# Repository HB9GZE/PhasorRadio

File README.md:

# PhasorRadio
Phasor-Radio for 20m/40m and 80m with 5 Watt ERP Amp

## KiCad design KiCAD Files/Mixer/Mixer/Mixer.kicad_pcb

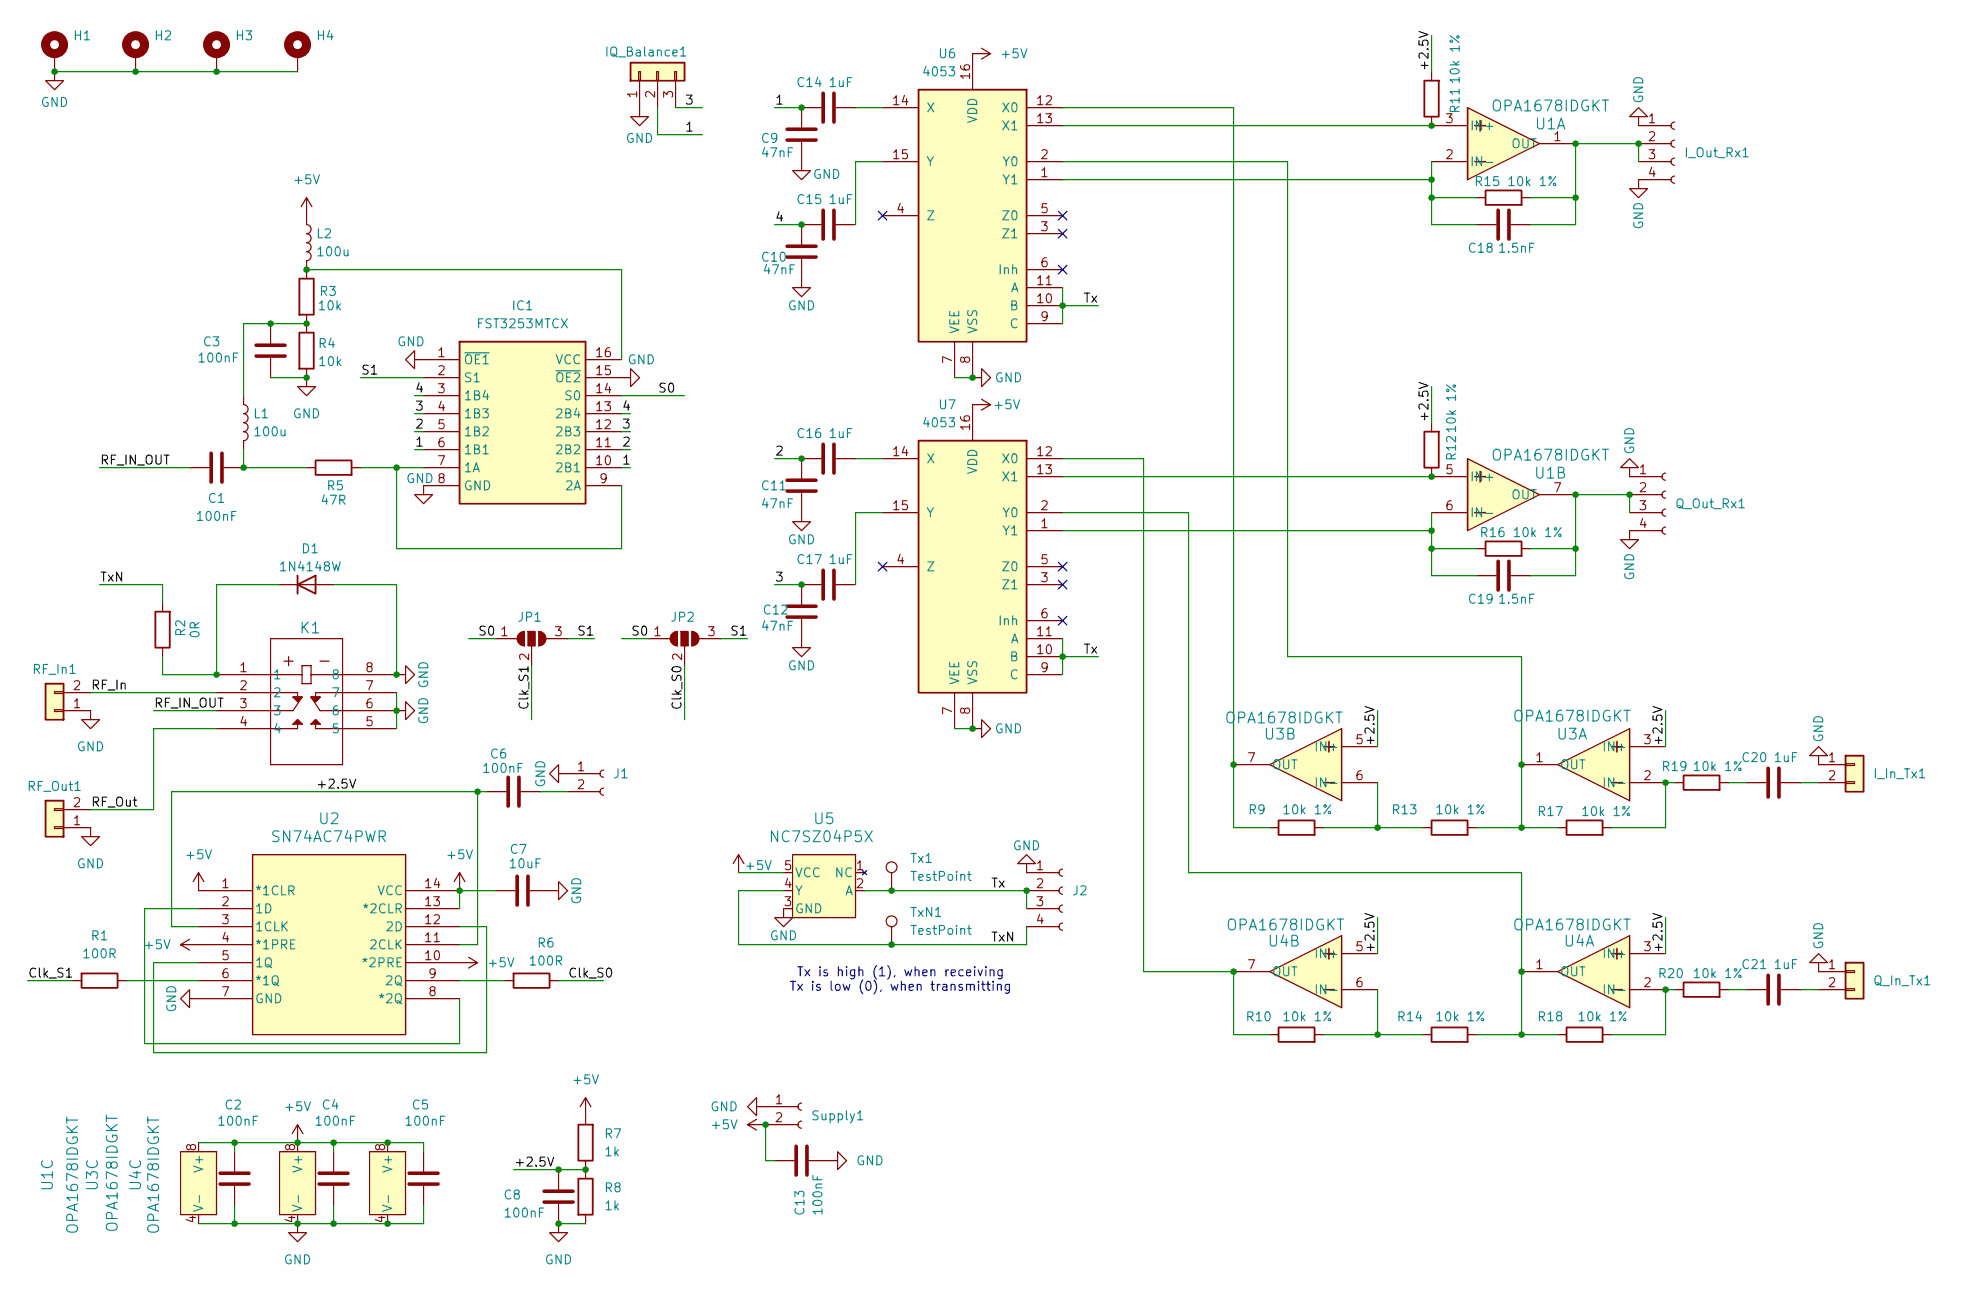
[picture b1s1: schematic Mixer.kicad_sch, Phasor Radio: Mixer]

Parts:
C1, C2, C3, C4, C5, C8, C13: 100nF; C_0805_2012Metric_Pad1.18x1.45mm_HandSolder
C6: 100nF; C_0603_1608Metric_Pad1.08x0.95mm_HandSolder
C7: 10uF; C_0805_2012Metric_Pad1.18x1.45mm_HandSolder
C9, C10, C11, C12: 47nF; C_0805_2012Metric_Pad1.18x1.45mm_HandSolder
C14, C15, C16, C17, C20, C21: 1uF; C_0805_2012Metric_Pad1.18x1.45mm_HandSolder
C18, C19: 1.5nF; C_0805_2012Metric_Pad1.18x1.45mm_HandSolder
D1: 1N4148W; D_SOD-123
H1, H2, H3, H4: MountingHole_Pad; MountingHole_2.7mm_M2.5_DIN965_Pad_TopBottom
IC1: FST3253MTCX; SOP65P640X110-16N; Manufacturer_Part_Number FST3253MTCX; Mouser Part Number 512-FST3253MTCX
IQ_Balance1: Conn_01x03; PinHeader_1x03_P1.00mm_Vertical
I_In_Tx1: Conn_01x02; JST_EH_B2B-EH-A_1x02_P2.50mm_Vertical
I_Out_Rx1: Conn_01x04_Socket; JST_EH_B4B-EH-A_1x04_P2.50mm_Vertical
J1: Conn_01x02_Socket; JST_EH_B2B-EH-A_1x02_P2.50mm_Vertical
J2: Conn_01x04_Socket; JST_EH_B4B-EH-A_1x04_P2.50mm_Vertical
JP1, JP2: SolderJumper_3_Open; SolderJumper-3_P1.3mm_Open_Pad1.0x1.5mm_NumberLabels
K1: G6K-2F-Y DC3; G6K-2F-Y DC3_OMR
L1, L2: 100u; L_0805_2012Metric_Pad1.15x1.40mm_HandSolder
Q_In_Tx1: Conn_01x02; JST_EH_B2B-EH-A_1x02_P2.50mm_Vertical
Q_Out_Rx1: Conn_01x04_Socket; JST_EH_B4B-EH-A_1x04_P2.50mm_Vertical
R1, R6: 100R; R_0603_1608Metric_Pad0.98x0.95mm_HandSolder
R2: 0R; R_0805_2012Metric_Pad1.20x1.40mm_HandSolder
R3, R4: 10k; R_0805_2012Metric_Pad1.20x1.40mm_HandSolder
R5: 47R; R_0805_2012Metric_Pad1.20x1.40mm_HandSolder
R7, R8: 1k; R_0805_2012Metric_Pad1.20x1.40mm_HandSolder
R9, R10, R11, R12, R13, R14, R15, R16, R17, R18, R19, R20: 10k 1%; R_0805_2012Metric_Pad1.20x1.40mm_HandSolder
RF_In1: Conn_01x02; PinHeader_1x02_P2.54mm_Vertical
RF_Out1: Conn_01x02; PinHeader_1x02_P2.54mm_Vertical
Supply1: Conn_01x02_Socket; JST_EH_B2B-EH-A_1x02_P2.50mm_Vertical
Tx1: TestPoint; Pin_D0.7mm_L6.5mm_W1.8mm_FlatFork
TxN1: TestPoint; Pin_D0.7mm_L6.5mm_W1.8mm_FlatFork
U1, U3, U4: OPA1678IDGKT; OPA1678_L
U2: SN74AC74PWR; 74AC74-L
U5: NC7SZ04P5X; SC-88A-5_1P35X2P2_ONS
U6, U7: 4053; TSSOP16_5P1X4P5_NEX

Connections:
+5V: C2.2, C4.2, C5.2, C7.2, C13.2, L2.1, R7.2, Supply1.2, U1.8 (V+), U2.1 (*1CLR), U2.4 (*1PRE), U2.10 (*2PRE), U2.13 (*2CLR), U2.14 (VCC), U3.8 (V+), U4.8 (V+), U5.5 (VCC), U6.16 (VDD), U7.16 (VDD)
/1: C9.2, C14.2, IC1.6 (1B1), IC1.10 (2B1), IQ_Balance1.2
/2: C11.2, C16.2, IC1.5 (1B2), IC1.11 (2B2)
/3: C12.2, C17.2, IC1.4 (1B3), IC1.12 (2B3), IQ_Balance1.3
/4: C10.2, C15.2, IC1.3 (1B4), IC1.13 (2B4)
/+2.5V: C6.2, C8.2, R7.1, R8.1, R11.2, R12.2, U2.3 (1CLK), U2.11 (2CLK), U3.3 (IN+), U3.5 (IN+), U4.3 (IN+), U4.5 (IN+)
/Clk_S1: JP1.2 (C), R1.2
/RF_IN_OUT: C1.1, K1.3
/RF_In: K1.2, RF_In1.2
/RF_Out: K1.4, RF_Out1.2
/S1: IC1.2 (S1), JP1.3 (B), JP2.3 (B)
/Tx: J2.2, J2.3, Tx1.1, U5.2 (A), U6.9 (C), U6.10 (B), U6.11 (A), U7.9 (C), U7.10 (B), U7.11 (A)
/TxN: J2.4, R2.2, TxN1.1, U5.4 (Y)
GND: C2.1, C3.1, C4.1, C5.1, C7.1, C8.1, C9.1, C10.1, C11.1, C12.1, C13.1, D1.2 (A), H1.1, H2.1, H3.1, H4.1, IC1.1 (~OE1), IC1.8 (GND), IC1.15 (~OE2), IQ_Balance1.1, I_In_Tx1.1, I_Out_Rx1.1, I_Out_Rx1.4, J1.1, J2.1, K1.5, K1.6, K1.7, K1.8, Q_In_Tx1.1, Q_Out_Rx1.1, Q_Out_Rx1.4, R4.2, R8.2, RF_In1.1, RF_Out1.1, Supply1.1, U1.4 (V-), U2.7 (GND), U3.4 (V-), U4.4 (V-), U5.3 (GND), U6.7 (VEE), U6.8 (VSS), U7.7 (VEE), U7.8 (VSS)
unnamed: C1.2, L1.2, R5.1
unnamed: C3.2, L1.1, R3.2, R4.1
unnamed: C20.2, R19.2
unnamed: C21.2, R20.2
unnamed: D1.1 (K), K1.1, R2.1
unnamed: IC1.7 (1A), IC1.9 (2A), R5.2
unnamed: IC1.16 (VCC), L2.2, R3.1
unnamed: C20.1, I_In_Tx1.2
unnamed: C18.1, I_Out_Rx1.2, I_Out_Rx1.3, R15.2, U1.1 (OUT)
unnamed: C6.1, J1.2
unnamed: C21.1, Q_In_Tx1.2
unnamed: C19.1, Q_Out_Rx1.2, Q_Out_Rx1.3, R16.2, U1.7 (OUT)
unnamed: R11.1, U1.3 (IN+), U6.13 (X1)
unnamed: C18.2, R15.1, U1.2 (IN-), U6.1 (Y1)
unnamed: R12.1, U1.5 (IN+), U7.13 (X1)
unnamed: C19.2, R16.1, U1.6 (IN-), U7.1 (Y1)
unnamed: U2.5 (1Q), U2.12 (2D)
unnamed: R6.2, U2.9 (2Q)
unnamed: R1.1, U2.6 (*1Q)
unnamed: U2.2 (1D), U2.8 (*2Q)
unnamed: R17.2, R19.1, U3.2 (IN-)
unnamed: R13.2, R17.1, U3.1 (OUT), U6.2 (Y0)
unnamed: R9.2, R13.1, U3.6 (IN-)
unnamed: R9.1, U3.7 (OUT), U6.12 (X0)
unnamed: R18.2, R20.1, U4.2 (IN-)
unnamed: R14.2, R18.1, U4.1 (OUT), U7.2 (Y0)
unnamed: R10.2, R14.1, U4.6 (IN-)
unnamed: R10.1, U4.7 (OUT), U7.12 (X0)
unnamed: C14.1, U6.14 (X)
unnamed: C15.1, U6.15 (Y)
unnamed: C16.1, U7.14 (X)
unnamed: C17.1, U7.15 (Y)

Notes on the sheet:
Tx is high (1), when receiving Tx is low (0), when transmitting

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
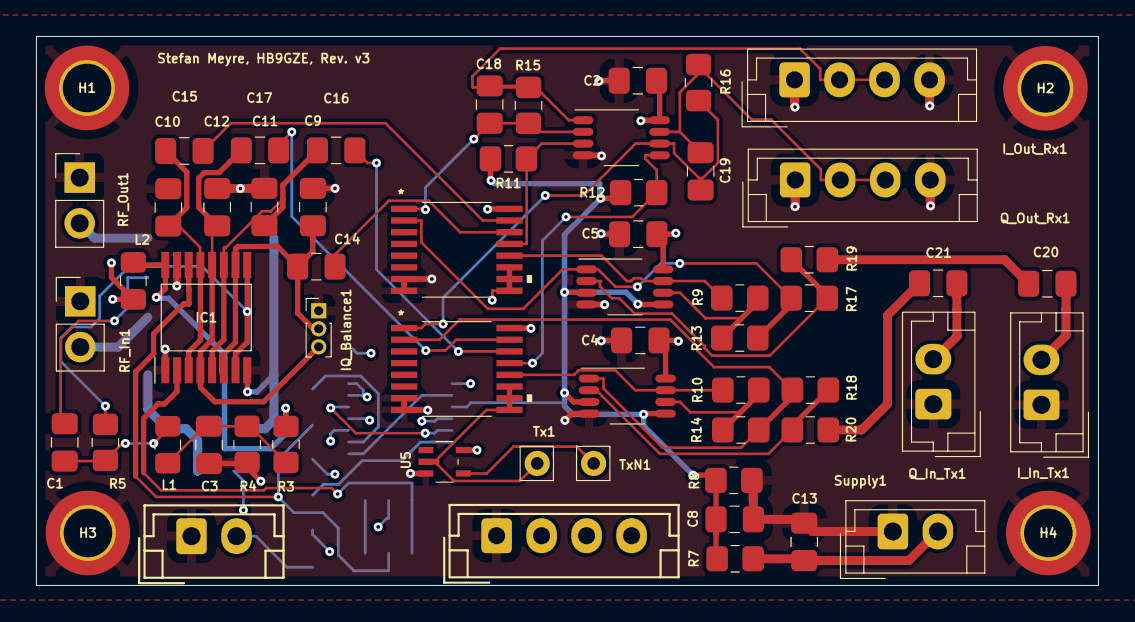
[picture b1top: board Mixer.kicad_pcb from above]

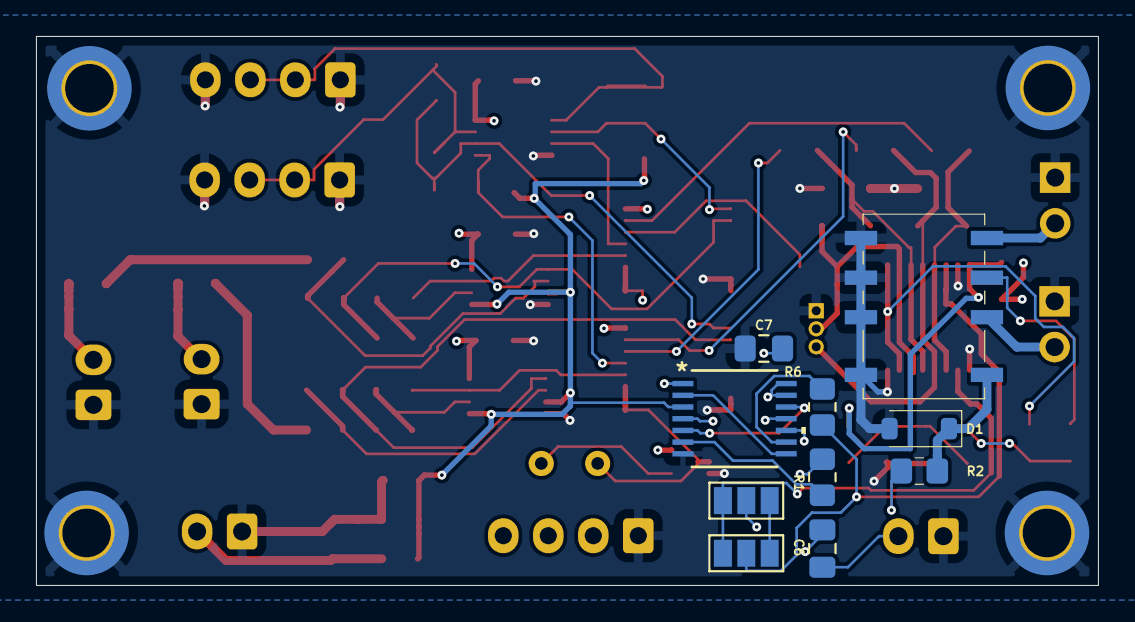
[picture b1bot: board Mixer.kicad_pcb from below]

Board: 4 copper layers, 59.0 x 30.5 mm, 71 parts (10 on the bottom side), 48 nets.

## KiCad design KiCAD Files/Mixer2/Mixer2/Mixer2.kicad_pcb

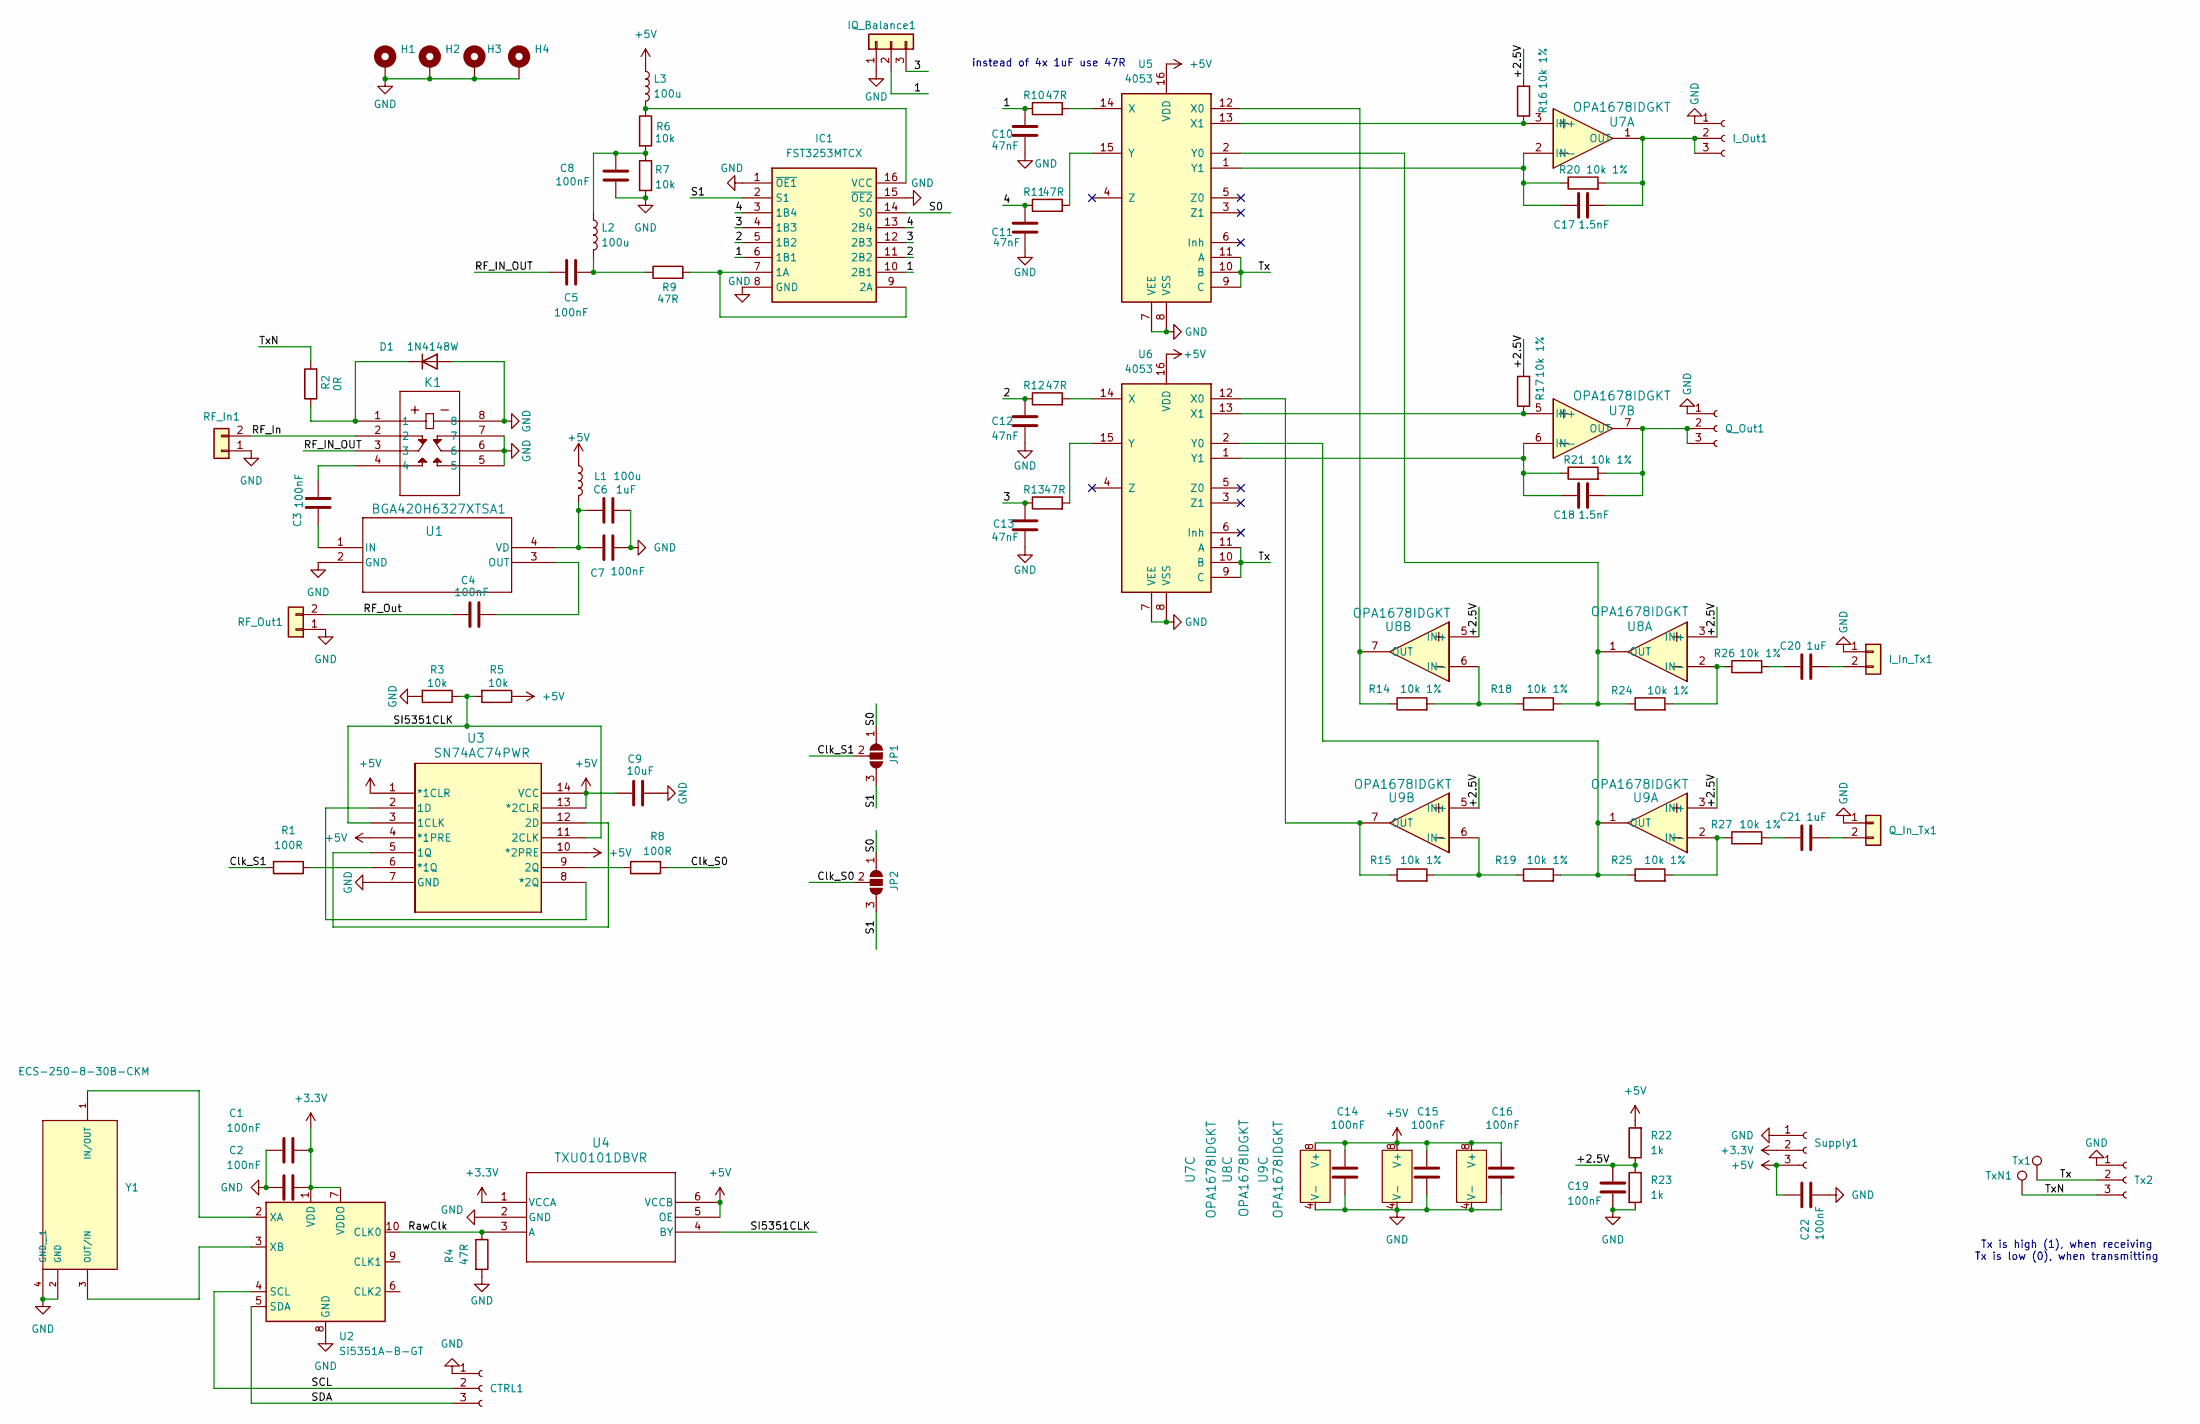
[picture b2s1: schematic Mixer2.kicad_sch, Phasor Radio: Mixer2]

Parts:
C1, C2, C3, C4, C5, C7, C8, C14, C15, C16, C19, C22: 100nF; C_0603_1608Metric_Pad1.08x0.95mm_HandSolder
C6, C20, C21: 1uF; C_0603_1608Metric_Pad1.08x0.95mm_HandSolder
C9: 10uF; C_0603_1608Metric_Pad1.08x0.95mm_HandSolder
C10, C11, C12, C13: 47nF; C_0603_1608Metric_Pad1.08x0.95mm_HandSolder
C17, C18: 1.5nF; C_0603_1608Metric_Pad1.08x0.95mm_HandSolder
CTRL1: Conn_01x03_Socket; JST_EH_B3B-EH-A_1x03_P2.50mm_Vertical
D1: 1N4148W; D_SOD-123
H1, H2, H3, H4: MountingHole_Pad; MountingHole_2.7mm_M2.5_DIN965_Pad_TopBottom
IC1: FST3253MTCX; SOP65P640X110-16N; Manufacturer_Part_Number FST3253MTCX; Mouser Part Number 512-FST3253MTCX
IQ_Balance1: Conn_01x03; PinHeader_1x03_P1.00mm_Vertical
I_In_Tx1: Conn_01x02; JST_EH_B2B-EH-A_1x02_P2.50mm_Vertical
I_Out1: I_Out; JST_EH_B3B-EH-A_1x03_P2.50mm_Vertical
JP1, JP2: SolderJumper_3_Open; SolderJumper-3_P1.3mm_Open_Pad1.0x1.5mm_NumberLabels
K1: G6K-2F-Y DC3; G6K-2F-Y DC3_OMR
L1, L2, L3: 100u; L_0805_2012Metric_Pad1.15x1.40mm_HandSolder
Q_In_Tx1: Conn_01x02; JST_EH_B2B-EH-A_1x02_P2.50mm_Vertical
Q_Out1: Q_Out; JST_EH_B3B-EH-A_1x03_P2.50mm_Vertical
R1, R8: 100R; R_0603_1608Metric_Pad0.98x0.95mm_HandSolder
R2: 0R; R_0603_1608Metric_Pad0.98x0.95mm_HandSolder
R3, R5, R6, R7: 10k; R_0603_1608Metric_Pad0.98x0.95mm_HandSolder
R4, R9, R10, R11, R12, R13: 47R; R_0603_1608Metric_Pad0.98x0.95mm_HandSolder
R14, R15, R16, R17, R18, R19, R20, R21, R24, R25, R26, R27: 10k 1%; R_0603_1608Metric_Pad0.98x0.95mm_HandSolder
R22, R23: 1k; R_0603_1608Metric_Pad0.98x0.95mm_HandSolder
RF_In1: Conn_01x02; PinHeader_1x02_P2.54mm_Vertical
RF_Out1: Conn_01x02; PinHeader_1x02_P2.54mm_Vertical
Supply1: Supply; JST_EH_B3B-EH-A_1x03_P2.50mm_Vertical
Tx1: TestPoint; Pin_D0.7mm_L6.5mm_W1.8mm_FlatFork
Tx2: Q_Out; JST_EH_B3B-EH-A_1x03_P2.50mm_Vertical
TxN1: TestPoint; Pin_D0.7mm_L6.5mm_W1.8mm_FlatFork
U1: BGA420H6327XTSA1; PG-SOT343-4-1_INF
U2: Si5351A-B-GT; MSOP-10_3x3mm_P0.5mm
U3: SN74AC74PWR; 74AC74-L
U4: TXU0101DBVR; SOT-23-6-DBV_TEX
U5, U6: 4053; TSSOP16_5P1X4P5_NEX
U7, U8, U9: OPA1678IDGKT; OPA1678_L
Y1: ECS-250-8-30B-CKM; XTAL_ECS-250-8-30B-CKM

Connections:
+3.3V: C1.2, C2.2, Supply1.2, U2.1 (VDD), U2.7 (VDDO), U4.1 (VCCA)
+5V: C9.2, C14.2, C15.2, C16.2, C22.2, L1.1, L3.1, R5.1, R22.2, Supply1.3, U3.1 (*1CLR), U3.4 (*1PRE), U3.10 (*2PRE), U3.13 (*2CLR), U3.14 (VCC), U4.5 (OE), U4.6 (VCCB), U5.16 (VDD), U6.16 (VDD), U7.8 (V+), U8.8 (V+), U9.8 (V+)
/1: C10.2, IC1.6 (1B1), IC1.10 (2B1), IQ_Balance1.2, R10.1
/2: C12.2, IC1.5 (1B2), IC1.11 (2B2), R12.1
/3: C13.2, IC1.4 (1B3), IC1.12 (2B3), IQ_Balance1.3, R13.1
/4: C11.2, IC1.3 (1B4), IC1.13 (2B4), R11.1
/+2.5V: C19.2, R16.2, R17.2, R22.1, R23.1, U8.3 (IN+), U8.5 (IN+), U9.3 (IN+), U9.5 (IN+)
/Clk_S0: JP2.2 (C), R8.1
/Clk_S1: JP1.2 (C), R1.2
/RF_IN_OUT: C5.1, K1.3
/RF_In: K1.2, RF_In1.2
/RF_Out: C4.2, RF_Out1.2
/RawClk: R4.1, U2.10 (CLK0), U4.3 (A)
/S0: IC1.14 (S0), JP1.1 (A), JP2.1 (A)
/S1: IC1.2 (S1), JP1.3 (B), JP2.3 (B)
/SCL: CTRL1.2, U2.4 (SCL)
/SDA: CTRL1.3, U2.5 (SDA)
/SI5351CLK: R3.1, R5.2, U3.3 (1CLK), U3.11 (2CLK), U4.4 (BY)
/Tx: Tx1.1, Tx2.2, U5.9 (C), U5.10 (B), U5.11 (A), U6.9 (C), U6.10 (B), U6.11 (A)
/TxN: R2.2, Tx2.3, TxN1.1
GND: C1.1, C2.1, C6.1, C7.1, C8.1, C9.1, C10.1, C11.1, C12.1, C13.1, C14.1, C15.1, C16.1, C19.1, C22.1, CTRL1.1, D1.2 (A), H1.1, H2.1, H3.1, H4.1, IC1.1 (~OE1), IC1.8 (GND), IC1.15 (~OE2), IQ_Balance1.1, I_In_Tx1.1, I_Out1.1, K1.5, K1.6, K1.7, K1.8, Q_In_Tx1.1, Q_Out1.1, R3.2, R4.2, R7.2, R23.2, RF_In1.1, RF_Out1.1, Supply1.1, Tx2.1, U1.2 (GND), U2.8 (GND), U3.7 (GND), U4.2 (GND), U5.7 (VEE), U5.8 (VSS), U6.7 (VEE), U6.8 (VSS), U7.4 (V-), U8.4 (V-), U9.4 (V-), Y1.2 (GND), Y1.4 (GND__1)
unnamed: C3.1, K1.4
unnamed: C5.2, L2.2, R9.1
unnamed: C8.2, L2.1, R6.2, R7.1
unnamed: C20.2, R26.2
unnamed: C21.2, R27.2
unnamed: D1.1 (K), K1.1, R2.1
unnamed: IC1.7 (1A), IC1.9 (2A), R9.2
unnamed: IC1.16 (VCC), L3.2, R6.1
unnamed: C20.1, I_In_Tx1.2
unnamed: C17.1, I_Out1.2, I_Out1.3, R20.2, U7.1 (OUT)
unnamed: C21.1, Q_In_Tx1.2
unnamed: C18.1, Q_Out1.2, Q_Out1.3, R21.2, U7.7 (OUT)
unnamed: C3.2, U1.1 (IN)
unnamed: C4.1, U1.3 (OUT)
unnamed: C6.2, C7.2, L1.2, U1.4 (VD)
unnamed: U2.2 (XA), Y1.1 (IN/OUT)
unnamed: U2.3 (XB), Y1.3 (OUT/IN)
unnamed: U3.5 (1Q), U3.12 (2D)
unnamed: R8.2, U3.9 (2Q)
unnamed: R1.1, U3.6 (*1Q)
unnamed: U3.2 (1D), U3.8 (*2Q)
unnamed: R14.1, U5.12 (X0), U8.7 (OUT)
unnamed: R16.1, U5.13 (X1), U7.3 (IN+)
unnamed: R10.2, U5.14 (X)
unnamed: R18.2, R24.1, U5.2 (Y0), U8.1 (OUT)
unnamed: C17.2, R20.1, U5.1 (Y1), U7.2 (IN-)
unnamed: R11.2, U5.15 (Y)
unnamed: R15.1, U6.12 (X0), U9.7 (OUT)
unnamed: R17.1, U6.13 (X1), U7.5 (IN+)
unnamed: R12.2, U6.14 (X)
unnamed: R19.2, R25.1, U6.2 (Y0), U9.1 (OUT)
unnamed: C18.2, R21.1, U6.1 (Y1), U7.6 (IN-)
unnamed: R13.2, U6.15 (Y)
unnamed: R24.2, R26.1, U8.2 (IN-)
unnamed: R14.2, R18.1, U8.6 (IN-)
unnamed: R25.2, R27.1, U9.2 (IN-)
unnamed: R15.2, R19.1, U9.6 (IN-)

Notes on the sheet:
instead of 4x 1uF use 47R
Tx is high (1), when receiving Tx is low (0), when transmitting

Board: 4 copper layers, 83 parts (27 on the bottom side), 58 nets, no tracks yet.
